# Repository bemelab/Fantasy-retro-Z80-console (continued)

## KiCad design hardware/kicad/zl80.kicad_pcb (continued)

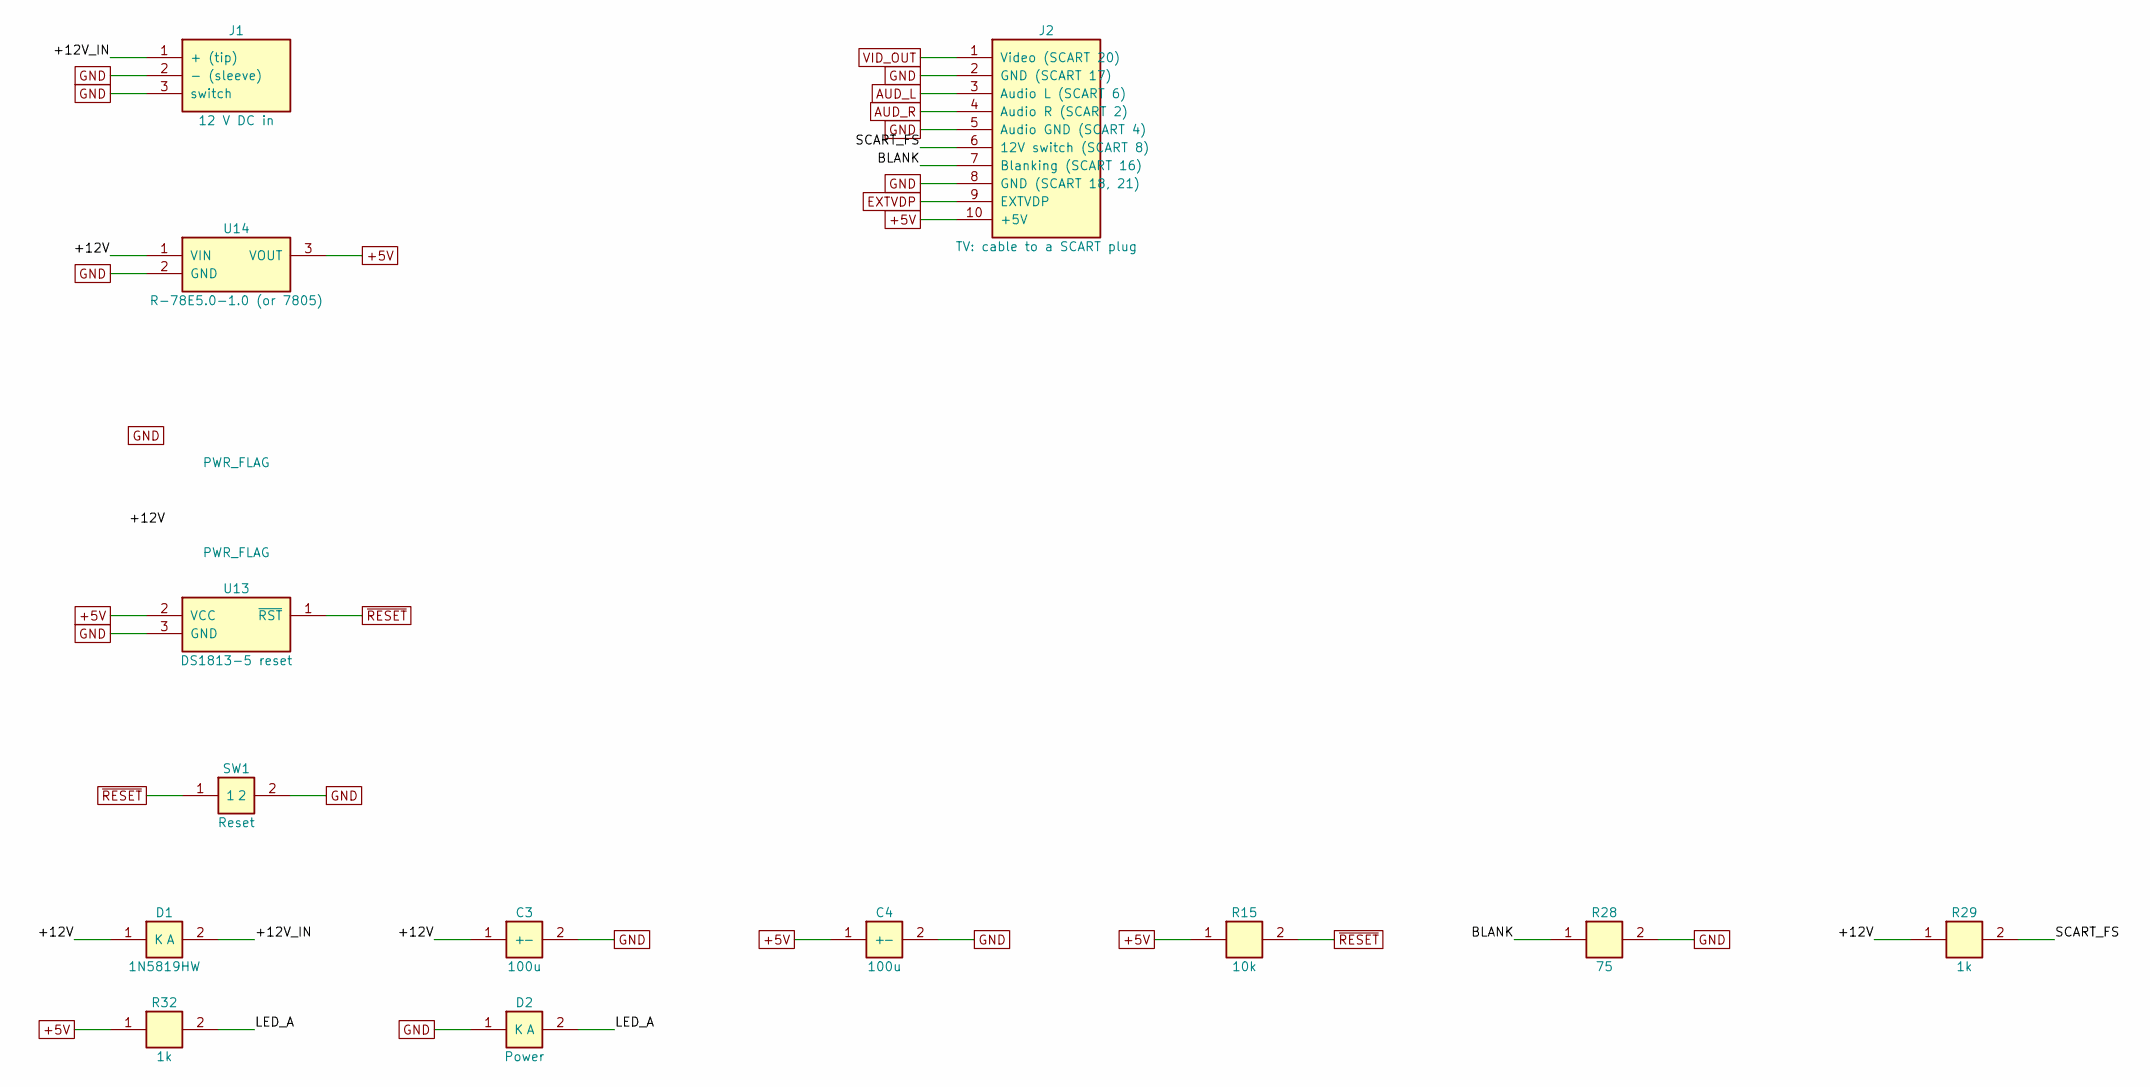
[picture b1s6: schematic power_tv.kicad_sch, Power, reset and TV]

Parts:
C3, C4: 100u; CP_Elec_6.3x7.7
D1: 1N5819HW; D_SOD-123
D2: Power; LED_0805_2012Metric
J1: 12 V DC in; BarrelJack_Horizontal
J2: TV: cable to a SCART plug; PinHeader_2x05_P2.54mm_Vertical
R15: 10k; R_0805_2012Metric
R28: 75; R_0805_2012Metric
R29, R32: 1k; R_0805_2012Metric
SW1: Reset; SW_SPST_B3U-1000P
U13: DS1813-5 reset; SOT-23-3
U14: R-78E5.0-1.0 (or 7805); Converter_DCDC_RECOM_R-78E-0.5_THT

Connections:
+5V: C4.1 (+), J2.10 (+5V), R15.1, R32.1, U13.2 (VCC), U14.3 (VOUT); also elsewhere on the board
+12V: C3.1 (+), D1.1 (K), R29.1, U14.1 (VIN)
+12V_IN: D1.2 (A), J1.1 (+ (tip))
AUD_L: J2.3 (Audio L (SCART 6)); also elsewhere on the board
AUD_R: J2.4 (Audio R (SCART 2)); also elsewhere on the board
BLANK: J2.7 (Blanking (SCART 16)), R28.1
EXTVDP: J2.9 (EXTVDP); also elsewhere on the board
GND: C3.2 (-), C4.2 (-), D2.1 (K), J1.2 (- (sleeve)), J1.3 (switch), J2.2 (GND (SCART 17)), J2.5 (Audio GND (SCART 4)), J2.8 (GND (SCART 18, 21)), R28.2, SW1.2, U13.3 (GND), U14.2 (GND); also elsewhere on the board
LED_A: D2.2 (A), R32.2
SCART_FS: J2.6 (12V switch (SCART 8)), R29.2
VID_OUT: J2.1 (Video (SCART 20)); also elsewhere on the board
~RESET: R15.2, SW1.1, U13.1 (~RST); also elsewhere on the board

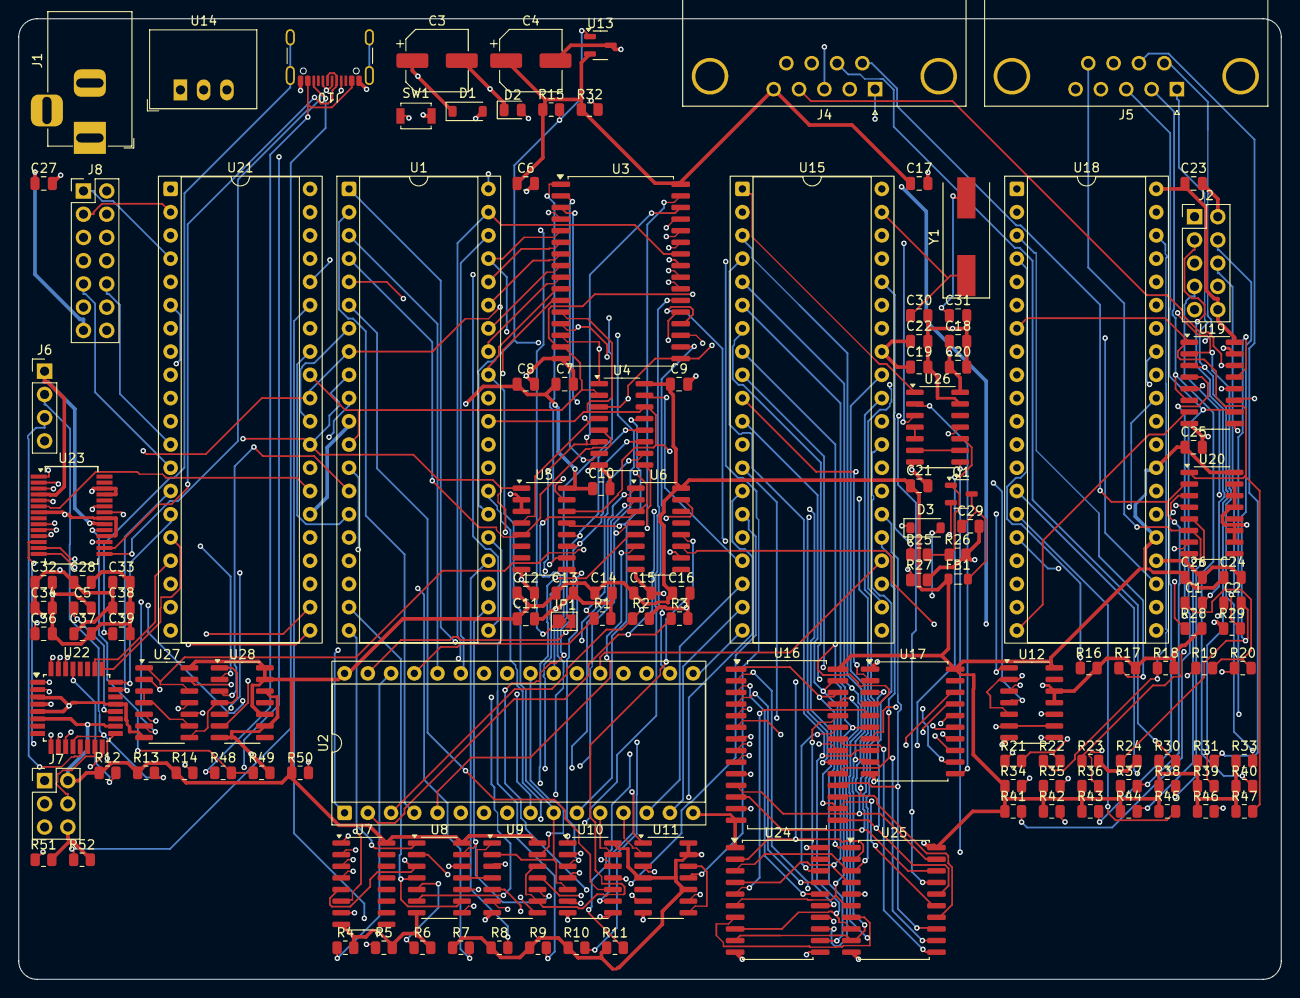
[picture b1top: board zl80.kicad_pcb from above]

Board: 4 copper layers, 138.0 x 105.0 mm, 134 parts (0 on the bottom side), 196 nets.

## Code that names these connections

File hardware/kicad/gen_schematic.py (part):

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PPI = Part("82C55A", [L(34, "D0", B), L(33, "D1", B), L(32, "D2", B), L(31, "D3", B), L(30, "D4", B), L(29, "D5", B),
                       L(28, "D6", B), L(27, "D7", B), None, L(6, "~{CS}", I), L(5, "~{RD}", I), L(36, "~{WR}", I),
                       L(9, "A0", I), L(8, "A1", I), L(35, "RESET", I), None, L(26, "VCC", PI), L(7, "GND", PI),
                       R(4, "PA0", B), R(3, "PA1", B), R(2, "PA2", B), R(1, "PA3", B), R(40, "PA4", B), R(39, "PA5", B),
                       R(38, "PA6", B), R(37, "PA7", B), ("gap", "R"),
                       R(18, "PB0", B), R(19, "PB1", B), R(20, "PB2", B), R(21, "PB3", B), R(22, "PB4", B), R(23, "PB5", B),
                       R(24, "PB6", B), R(25, "PB7", B), ("gap", "R"),
                       R(14, "PC0", B), R(15, "PC1", B), R(16, "PC2", B), R(17, "PC3", B), R(13, "PC4", B), R(12, "PC5", B),
                       R(11, "PC6", B), R(10, "PC7", B)],
           footprint=DIP40, width=22.86)

# FT245RL USB FIFO (FTDI DS_FT245R v2.14, SSOP-28). WR latches on its falling edge; the data bus order is scrambled.
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                           R(19, "Q0", O), R(18, "Q1", O), R(17, "Q2", O), R(16, "Q3", O), R(15, "Q4", O), R(14, "Q5", O),
                           R(13, "Q6", O), R(12, "Q7", O)], footprint=SO20W)

MCU = Part("ATmega328P-AU", [L(29, "PC6/~{RESET}", I), None, L(23, "PC0", B), L(24, "PC1", B), L(25, "PC2", B),
                              L(26, "PC3", B), L(27, "PC4", B), L(28, "PC5", B), L(19, "ADC6", P), L(22, "ADC7", P), None,
                              L(12, "PB0", B), L(13, "PB1", B), L(14, "PB2", B), L(15, "PB3/MOSI", B), L(16, "PB4/MISO", B),
                              L(17, "PB5/SCK", B), L(7, "PB6/XTAL1", B), L(8, "PB7/XTAL2", B), None,
                              L(4, "VCC", PI), L(6, "VCC", PI), L(18, "AVCC", PI), L(20, "AREF", P),
                              L(3, "GND", PI), L(5, "GND", PI), L(21, "GND", PI),
                              R(30, "PD0", B), R(31, "PD1", B), R(32, "PD2", B), R(1, "PD3", B), R(2, "PD4", B), R(9, "PD5", B),
                              R(10, "PD6", B), R(11, "PD7", B)], footprint="Package_QFP:TQFP-32_7x7mm_P0.8mm", width=22.86)

HC138 = Part("74HCT138", [L(1, "A", I), L(2, "B", I), L(3, "C", I), None, L(6, "G1", I), L(4, "~{G2A}", I), L(5, "~{G2B}", I),
                           None, L(16, "VCC", PI), L(8, "GND", PI),
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ISP = conn_part("AVR_ISP6", [(1, "MISO"), (2, "VCC"), (3, "SCK"), (4, "MOSI"), (5, "~{RESET}"), (6, "GND")],
                "Connector_PinHeader_2.54mm:PinHeader_2x03_P2.54mm_Vertical")
DCJACK = conn_part("Barrel_Jack", [(1, "+ (tip)"), (2, "- (sleeve)"), (3, "switch")], "Connector_BarrelJack:BarrelJack_Horizontal")
EXP = conn_part("Expansion_2x7", [(1, "PA0"), (2, "PA1"), (3, "PA2"), (4, "PA3"), (5, "PA4"), (6, "PA5"), (7, "PA6"),
                                  (8, "PA7"), (9, "PC4"), (10, "PC5"), (11, "PC6"), (12, "PC7"), (13, "+5V"), (14, "GND")],
                "Connector_PinHeader_2.54mm:PinHeader_2x07_P2.54mm_Vertical")


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    mem(SRAM, "U3", "AS6C4008 SRAM, pages 32-63", "~{RAMCS}", "~{WR}")
    pg.put(2, PAGE, "U4", "74HCT670 page bits 0-3",
           {"15": "D0", "1": "D1", "2": "D2", "3": "D3", "14": "A0", "13": "A1", "12": "~{PGWR}", "5": "A14", "4": "A15",
            "11": "~{PGEN}", "16": V, "8": G, "10": "PA14", "9": "PA15", "7": "PA16", "6": "PA17"})
    pg.put(2, PAGE, "U5", "74HCT670 page bits 4-5",
           {"15": "D4", "1": "D5", "2": G, "3": G, "14": "A0", "13": "A1", "12": "~{PGWR}", "5": "A14", "4": "A15",
            "11": "~{PGEN}", "16": V, "8": G, "10": "PA18", "9": "PA19", "7": None, "6": None})
    pg.put(2, HC74, "U11", "74HCT74 paging on / AY clock",
           {"2": "D0", "3": "~{ENWR}", "4": V, "1": "~{RESET}", "5": None, "6": "~{PGEN}",
            "12": "~{AYCLK}", "11": "CPUCLK", "10": V, "13": V, "9": "AYCLK", "8": "~{AYCLK}", "14": V, "7": G})
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           {"1": "A3", "2": "A4", "3": "A5", "6": "A6", "4": "A7", "5": "~{IOSEL}", "16": V, "8": G,
            "15": None, "14": None, "13": None, "12": None, "11": None, "10": None, "9": None, "7": "~{MAP_CS}"})
    pg.put(3, HC32, "U8", "74HCT32",
           {"1": "~{IORQ}", "2": "M1", "3": "~{IOSEL}", "4": "~{MREQ}", "5": "PA19", "6": "~{ROMCS}",
            "9": "~{MREQ}", "10": "~{PA19}", "8": "~{RAMCS}", "12": "~{MAP_CS}", "13": "~{WR}", "11": "~{MAPWR}", "14": V, "7": G})
    pg.put(0, HC32, "U9", "74HCT32",
           {"1": "~{MAPWR}", "2": "A2", "3": "~{PGWR}", "4": "~{MAPWR}", "5": "~{A2}", "6": "~{ENWR}",
            "9": "~{VDP_CS}", "10": "~{WR}", "8": "~{CSW}", "12": "~{VDP_CS}", "13": "~{RD}", "11": "~{CSR}", "14": V, "7": G})
    pg.put(0, HC04, "U10", "74HCT04",
           {"1": "~{M1}", "2": "M1", "3": "PA19", "4": "~{PA19}", "5": "A2", "6": "~{A2}", "9": "~{RESET}", "8": "RESET",
            "11": "CPUCLK", "10": "ZCLK", "13": "A0", "12": "~{A0}", "14": V, "7": G})
    pg.put(1, JMP, "JP1", "Flash write enable", {"1": "~{WR}", "2": "~{FLWE}"})
    for i, net in enumerate(["PA14", "PA15", "PA16", "PA17", "PA18", "PA19"]):
        pg.two(RES, f"R{1 + i}", "10k", net, G)  # paging off: the page lines read 0
    for i, net in enumerate(["~{NMI}", "~{WAIT}", "~{BUSRQ}", "~{INT}", "~{FLWE}"]):
        pg.two(RES, f"R{7 + i}", "10k", V, net)
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            "30": "KCOL0", "31": "KCOL1", "32": "KCOL2", "1": "KCOL3", "2": "KCOL4", "9": "KCOL5", "10": "KCOL6", "11": "KCOL7"})
    pg.put(1, PS2, "J6", "PS/2 keyboard (panel socket)", {"1": V, "2": "PS2_CLK", "3": "PS2_DATA", "4": G})
    pg.put(1, ISP, "J7", "ISP for the ATmega", {"1": "KB_MISO", "2": V, "3": "KB_SCK", "4": "KB_MOSI", "5": "KB_RST", "6": G})
    pg.put(0, EXP, "J8", "Expansion (8255 PA, PC4-7)",
           {"1": "PPA0", "2": "PPA1", "3": "PPA2", "4": "PPA3", "5": "PPA4", "6": "PPA5", "7": "PPA6", "8": "PPA7",
            "9": "PPC4", "10": "PPC5", "11": "PPC6", "12": "PPC7", "13": V, "14": G})
    usb = {str(p): d for p, d in zip([1, 5, 3, 11, 2, 9, 10, 6], D)}
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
